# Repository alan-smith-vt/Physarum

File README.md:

# Physarum

Code-first 3D drafting for an ELEGOO Saturn 4 Ultra 16K (resin, 14 × 19 µm pixels).
Designs are Python; output is a printable `.goo`.

## Layout (`slicer_preview/`)

| File | Role |
|---|---|
| `designs/*.py` | One file per design; each defines `PIECES` (and optional `SUPPORTS = True`) |
| `geometry.py` | Primitives: frames, solid columns, base lattice, quad-spiral columns, bridge struts |
| `modifiers.py` | Wrappers that carve existing pieces: chamfer, arches, vaults, grayscale, ID dots |
| `stl_slicer.py` | `stl_piece(path)` — bring in an external mesh |
| `compose.py` | Composites pieces into one volume (shared by preview and export) |
| `supports.py` | TPMS (lidinoid) lattice supports — slow, still experimental |
| `printer.py` | Printer specs + preview downsample factor |

## Workflow

```
cd slicer_preview
cp designs/template.py designs/my_part.py   # edit PIECES
python generate.py my_part                  # preview data (8× downsampled)
python server.py                            # → http://localhost:5555
python to_goo.py my_part                    # full-res → out/my_part.goo
python sdcp.py upload out/my_part.goo       # send to the printer over the network
python sdcp.py print my_part.goo --yes      # start it (ask the user first)
```

**Getting a print to the printer:** always `sdcp.py` (SDCP V3 over the LAN; full command list in its docstring:
status, files, watch, camera, ...). The printer's USB port is dead and we don't use the Elegoo software, so the
network is the only path. Printer last seen at 192.168.0.4; `sdcp.py discover` finds it.
Check the upload printed "Uploaded ..." before `print`: `print` starts whatever file of that name is already on
the printer, so a failed upload silently reprints the old version. Give each revision its own file name (e.g.
`part_v3.goo`), and check `status` shows the expected `TotalLayer`.

Coordinates are mm; X/Z = plate plane, Y = up.

## Notes

- `designs/whiteboard_box.py` printed great (Mar 2026) — good reference for lattice walls.
- `to_goo.py` keeps the template `.goo`'s bottom exposure on purpose. The Julia print's
  custom 30 s base fused it to the plate.
- `archive/`: the failed Julia print (generation takes ~16 h — don't rerun casually),
  decorative geometry (ropes/braids/textured columns), old outputs.

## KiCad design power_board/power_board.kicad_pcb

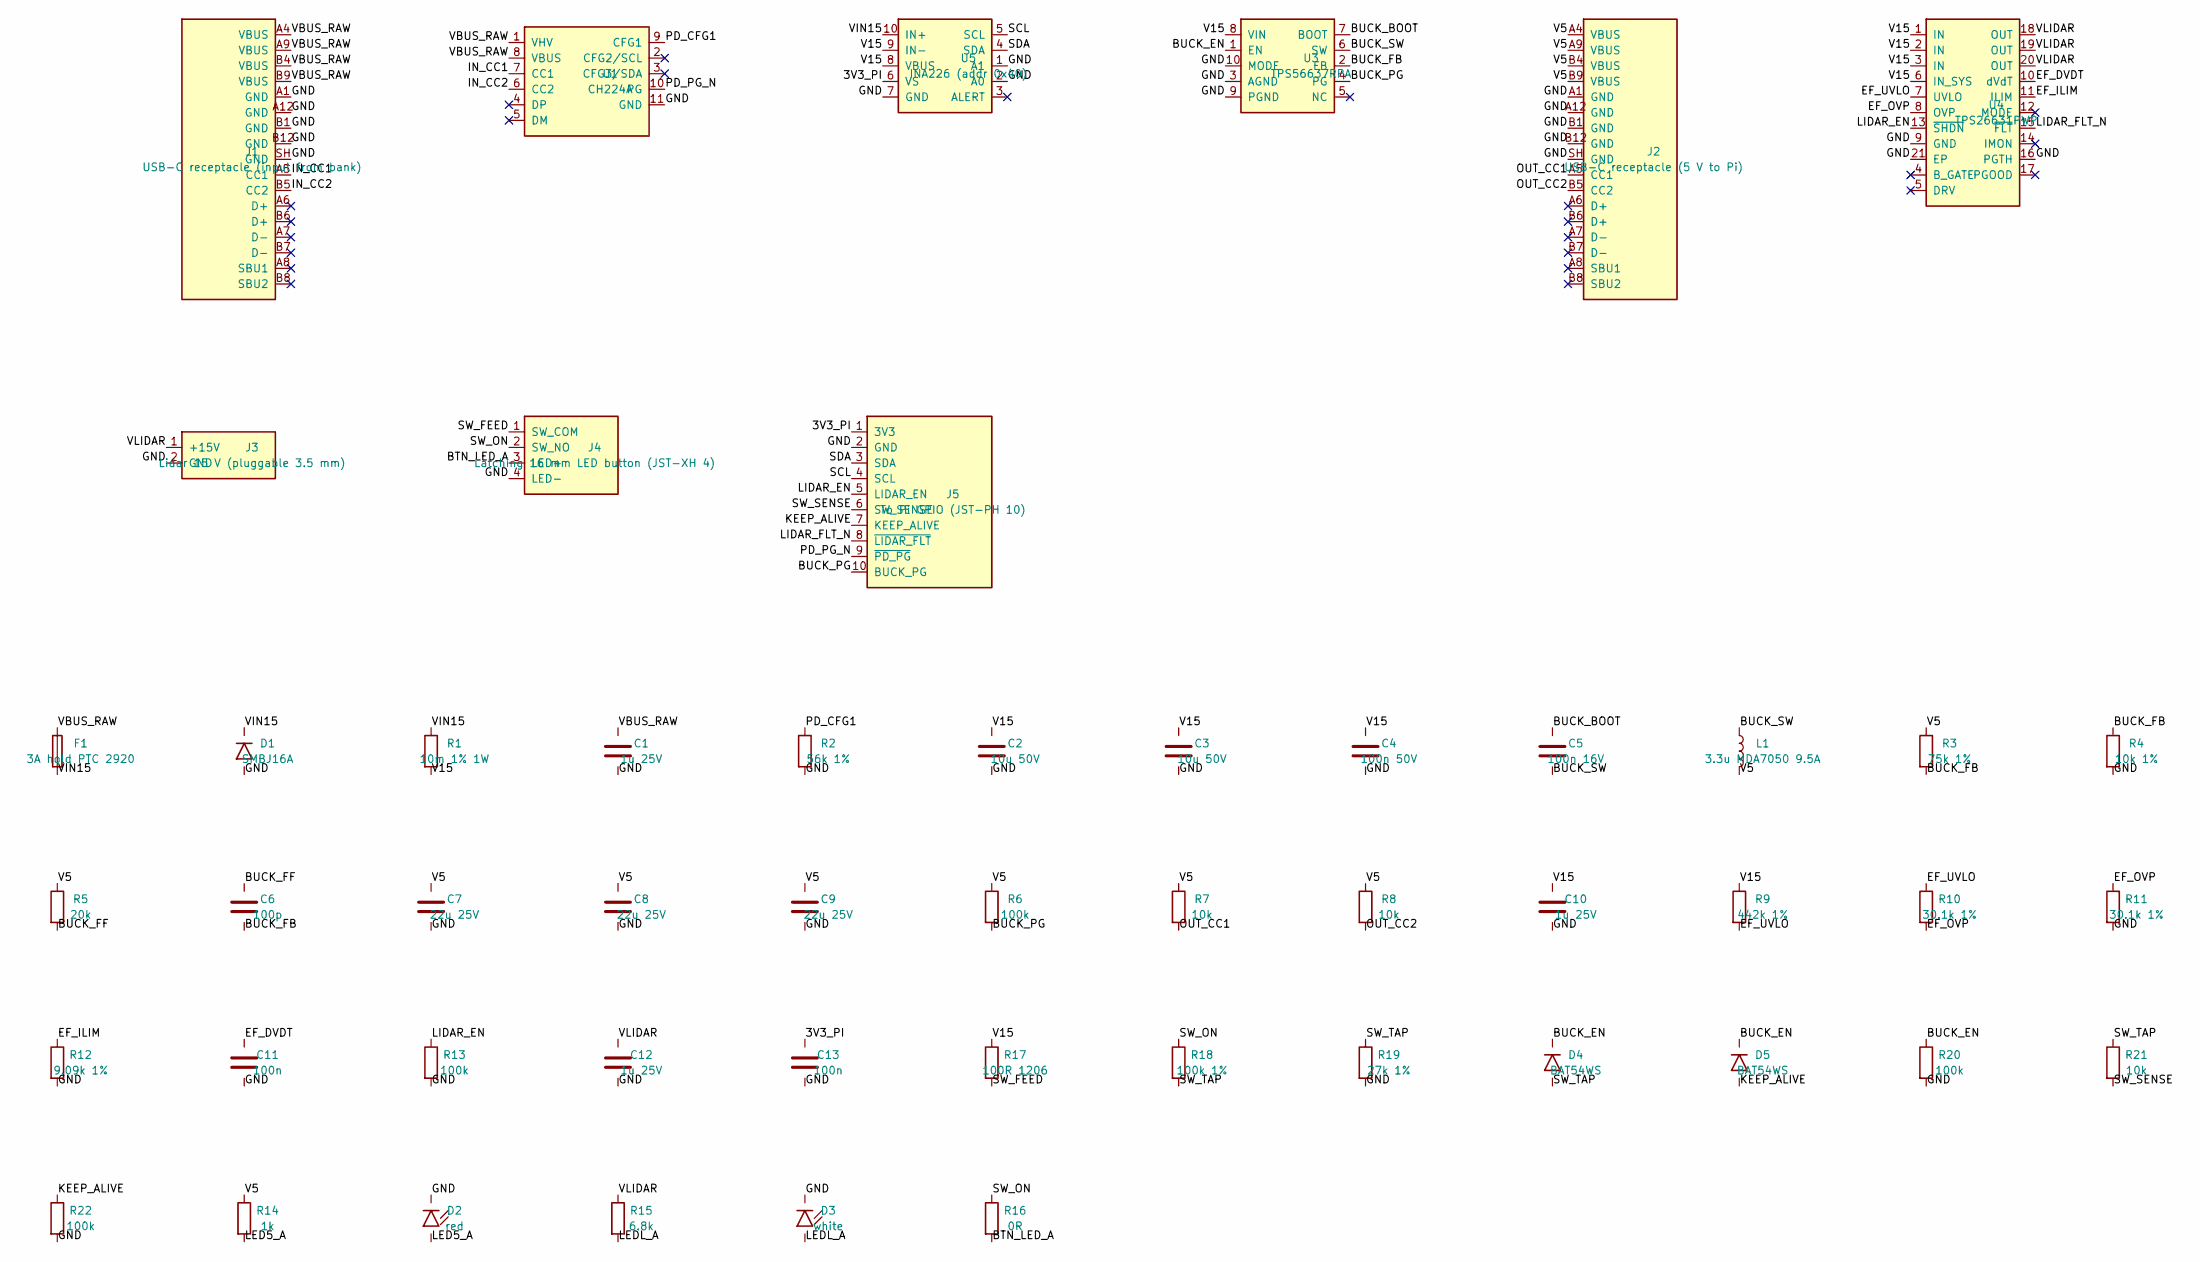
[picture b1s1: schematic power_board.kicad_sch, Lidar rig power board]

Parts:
C1, C10, C12: 1u 25V; C_0805_2012Metric
C2, C3: 10u 50V; C_1210_3225Metric
C4: 100n 50V; C_0603_1608Metric
C5: 100n 16V; C_0603_1608Metric
C6: 100p; C_0603_1608Metric
C7, C8, C9: 22u 25V; C_1210_3225Metric
C11, C13: 100n; C_0603_1608Metric
D1: SMBJ16A; D_SMB
D2: red; LED_0603_1608Metric
D3: white; LED_0603_1608Metric
D4, D5: BAT54WS; D_SOD-323
F1: 3A hold PTC 2920; Fuse_2920_7451Metric
J1: USB-C receptacle (input from bank); USB_C_Receptacle_HRO_TYPE-C-31-M-12
J2: USB-C receptacle (5 V to Pi); USB_C_Receptacle_HRO_TYPE-C-31-M-12
J3: Lidar 15 V (pluggable 3.5 mm); PhoenixContact_MCV_1,5_2-G-3.5_1x02_P3.50mm_Vertical
J4: Latching 16 mm LED button (JST-XH 4); JST_XH_B4B-XH-A_1x04_P2.50mm_Vertical
J5: To Pi GPIO (JST-PH 10); JST_PH_B10B-PH-K_1x10_P2.00mm_Vertical
L1: 3.3u MDA7050 9.5A; L_KOHERelec_MDA7030
R1: 10m 1% 1W; R_2512_6332Metric
R2: 56k 1%; R_0603_1608Metric
R3: 75k 1%; R_0603_1608Metric
R4: 10k 1%; R_0603_1608Metric
R5: 20k; R_0603_1608Metric
R6, R13, R20, R22: 100k; R_0603_1608Metric
R7, R8, R21: 10k; R_0603_1608Metric
R9: 442k 1%; R_0603_1608Metric
R10, R11: 30.1k 1%; R_0603_1608Metric
R12: 9.09k 1%; R_0603_1608Metric
R14: 1k; R_0603_1608Metric
R15: 6.8k; R_0603_1608Metric
R16: 0R; R_0603_1608Metric
R17: 100R 1206; R_1206_3216Metric
R18: 100k 1%; R_0603_1608Metric
R19: 27k 1%; R_0603_1608Metric
U1: CH224A; SSOP-10-1EP_3.9x4.9mm_P1mm_EP2.1x3.3mm
U3: TPS56637RPA; RPA0010A
U4: TPS26631PWP; HTSSOP-20-1EP_4.4x6.5mm_P0.65mm_EP3.4x6.5mm_Mask2.96x2.96mm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
U5: INA226 (addr 0x40); MSOP-10_3x3mm_P0.5mm

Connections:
/3V3_PI: C13.1, J5.1 (3V3), U5.6 (VS)
/BTN_LED_A: J4.3 (LED+), R16.2
/BUCK_BOOT: C5.1, U3.7 (BOOT)
/BUCK_EN: D4.1, D5.1, R20.1, U3.1 (EN)
/BUCK_FB: C6.2, R3.2, R4.1, U3.2 (FB)
/BUCK_FF: C6.1, R5.2
/BUCK_PG: J5.10 (BUCK_PG), R6.2, U3.4 (PG)
/BUCK_SW: C5.2, L1.1, U3.6 (SW)
/EF_DVDT: C11.1, U4.10 (dVdT)
/EF_ILIM: R12.1, U4.11 (ILIM)
/EF_OVP: R10.2, R11.1, U4.8 (OVP)
/EF_UVLO: R9.2, R10.1, U4.7 (UVLO)
/GND: C1.2, C2.2, C3.2, C4.2, C7.2, C8.2, C9.2, C10.2, C11.2, C12.2, C13.2, D1.2, D2.1, D3.1, J1.A1 (GND), J1.A12 (GND), J1.B1 (GND), J1.B12 (GND), J1.SH (GND), J2.A1 (GND), J2.A12 (GND), J2.B1 (GND), J2.B12 (GND), J2.SH (GND), J3.2 (GND), J4.4 (LED-), J5.2 (GND), R2.2, R4.2, R11.2, R12.2, R13.2, R19.2, R20.2, R22.2, U1.11 (GND), U3.3 (AGND), U3.9 (PGND), U3.10 (MODE), U4.9 (GND), U4.16 (PGTH), U4.21 (EP), U5.1 (A1), U5.2 (A0), U5.7 (GND)
/IN_CC1: J1.A5 (CC1), U1.7 (CC1)
/IN_CC2: J1.B5 (CC2), U1.6 (CC2)
/KEEP_ALIVE: D5.2, J5.7 (KEEP_ALIVE), R22.1
/LED5_A: D2.2, R14.2
/LEDL_A: D3.2, R15.2
/LIDAR_EN: J5.5 (LIDAR_EN), R13.1, U4.13 (~SHDN)
/LIDAR_FLT_N: J5.8 (~LIDAR_FLT), U4.15 (~FLT)
/OUT_CC1: J2.A5 (CC1), R7.2
/OUT_CC2: J2.B5 (CC2), R8.2
/PD_CFG1: R2.1, U1.9 (CFG1)
/PD_PG_N: J5.9 (~PD_PG), U1.10 (PG)
/SCL: J5.4 (SCL), U5.5 (SCL)
/SDA: J5.3 (SDA), U5.4 (SDA)
/SW_FEED: J4.1 (SW_COM), R17.2
/SW_ON: J4.2 (SW_NO), R16.1, R18.1
/SW_SENSE: J5.6 (SW_SENSE), R21.2
/SW_TAP: D4.2, R18.2, R19.1, R21.1
/V5: C7.1, C8.1, C9.1, J2.A4 (VBUS), J2.A9 (VBUS), J2.B4 (VBUS), J2.B9 (VBUS), L1.2, R3.1, R5.1, R6.1, R7.1, R8.1, R14.1
/V15: C2.1, C3.1, C4.1, C10.1, R1.2, R9.1, R17.1, U3.8 (VIN), U4.1 (IN), U4.2 (IN), U4.3 (IN), U4.6 (IN_SYS), U5.8 (VBUS), U5.9 (IN-)
/VBUS_RAW: C1.1, F1.1, J1.A4 (VBUS), J1.A9 (VBUS), J1.B4 (VBUS), J1.B9 (VBUS), U1.1 (VHV), U1.8 (VBUS)
/VIN15: D1.1, F1.2, R1.1, U5.10 (IN+)
/VLIDAR: C12.1, J3.1 (+15V), R15.1, U4.18 (OUT), U4.19 (OUT), U4.20 (OUT)

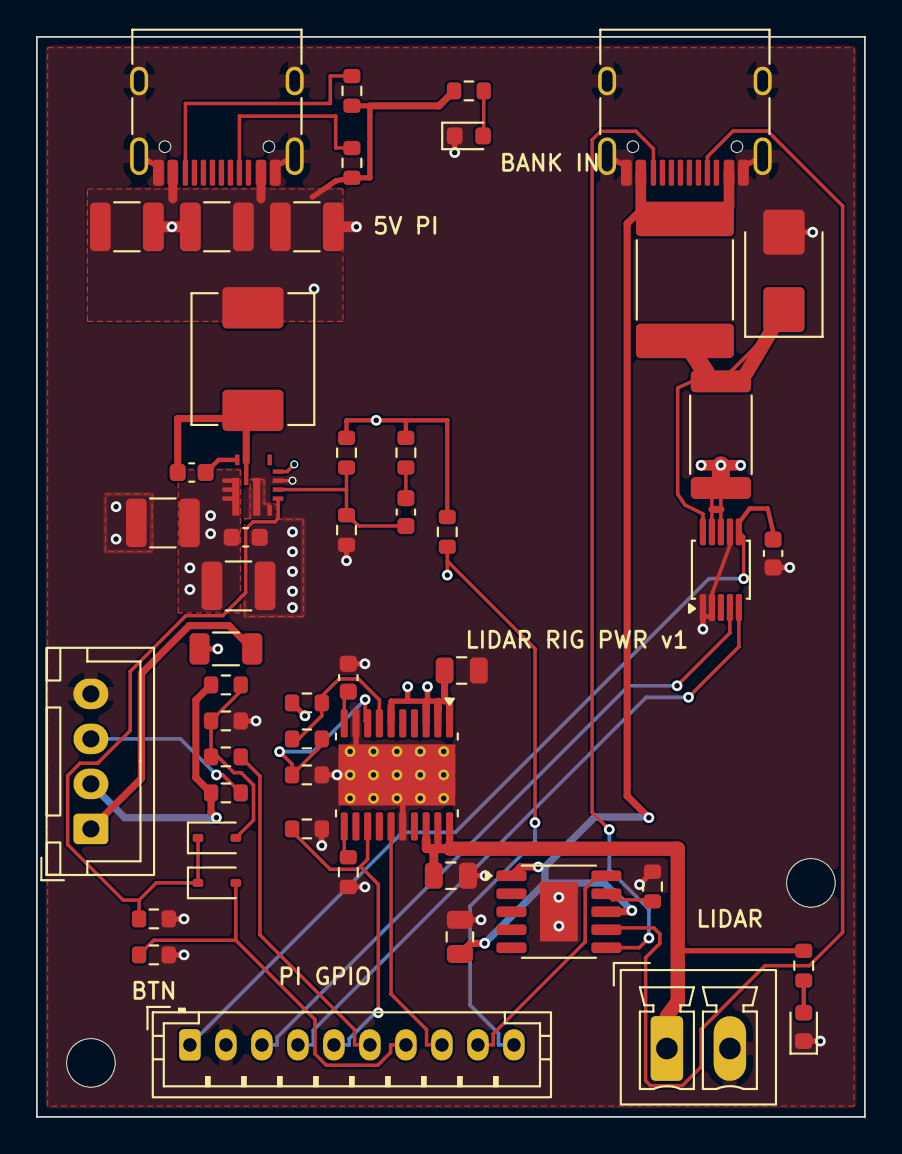
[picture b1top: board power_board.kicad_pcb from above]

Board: 4 copper layers, 46.0 x 60.0 mm, 53 parts (0 on the bottom side), 35 nets.

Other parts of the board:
H1, H2: MountingHole_2.7mm_M2.5

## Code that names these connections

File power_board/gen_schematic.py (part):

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    # INA226
    ("C13", "C", "100n", FP_C, "3V3_PI", "GND", "INA226 VS"),
    # Soft power with the latching switch: buck EN = switch OR Pi keep-alive (diode-OR).
    # Switch on: 15 V -> 100k/27k -> 3.19 V (safe for a Pi GPIO). Switch off: Pi sees SW_SENSE low,
    # shuts down, and drops KEEP_ALIVE at halt (gpio-poweroff), which turns the buck off.
    ("R17", "R", "100R 1206", "Resistor_SMD:R_1206_3216Metric", "V15", "SW_FEED", "limits a short in the switch lead; button LED (~10 mA) drops ~1 V"),
    ("R18", "R", "100k 1%", FP_R, "SW_ON", "SW_TAP", "switch divider top"),
    ("R19", "R", "27k 1%", FP_R, "SW_TAP", "GND", "switch divider bottom: 3.19 V"),
    ("D4", "D", "BAT54WS", "Diode_SMD:D_SOD-323", "BUCK_EN", "SW_TAP", "switch -> EN"),
    ("D5", "D", "BAT54WS", "Diode_SMD:D_SOD-323", "BUCK_EN", "KEEP_ALIVE", "Pi keep-alive -> EN"),
    ("R20", "R", "100k", FP_R, "BUCK_EN", "GND", "EN off when neither drives"),
    ("R21", "R", "10k", FP_R, "SW_TAP", "SW_SENSE", "series into Pi GPIO"),
    ("R22", "R", "100k", FP_R, "KEEP_ALIVE", "GND", "keep-alive low while Pi boots"),
    # Status LEDs
    ("R14", "R", "1k", FP_R, "V5", "LED5_A", ""),
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# side: "L" or "R"
ICS = [
    ("J1", "USB_C_SINK", "USB-C receptacle (input from bank)", "Connector_USB:USB_C_Receptacle_HRO_TYPE-C-31-M-12",
     usb_pins("VBUS_RAW", "IN_CC1", "IN_CC2", None, None, "R")),
    # CH224A: same function as the CH224Q in ESSOP-10 (hand-reworkable). CFG2/CFG3 have internal
    # 10k pull-ups to the chip's own rail, so they stay floating: tying them to the Pi's I2C would
    # back-power the Pi's 3V3 while the Pi is off. The INA226 reads the bus voltage instead.
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        ("4", "PG", "BUCK_PG", "R"), ("5", "NC", None, "R"),
    ]),
    ("J2", "USB_C_SOURCE", "USB-C receptacle (5 V to Pi)", "Connector_USB:USB_C_Receptacle_HRO_TYPE-C-31-M-12",
     usb_pins("V5", "OUT_CC1", "OUT_CC2", None, None, "L")),
    ("U4", "TPS26631", "TPS26631PWP", "Package_SO:HTSSOP-20-1EP_4.4x6.5mm_P0.65mm_EP3.4x6.5mm_Mask2.96x2.96mm_ThermalVias", [
        ("1", "IN", "V15", "L"), ("2", "IN", "V15", "L"), ("3", "IN", "V15", "L"),
        ("6", "IN_SYS", "V15", "L"), ("7", "UVLO", "EF_UVLO", "L"), ("8", "OVP", "EF_OVP", "L"),
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
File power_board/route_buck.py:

"""Route the TPS56637 buck on power_board.kicad_pcb (run after gen_board.py, with KiCad's Python).

Follows the datasheet layout guide (SLVSEG1A 10.1):
  - VIN loop: F.Cu V15 pour joining C3/C2/C4 to the pin-8 bar and fingers; C2 and C4 span VIN-PGND
    directly under the chip, their GND side in an F.Cu GND pour with stitching vias to In1/B.Cu.
  - SW: short 0.4 mm stub from pin 6 into L1, boot cap C5 beside pin 7.
  - VOUT: F.Cu V5 pour from L1 across the output caps to J2's VBUS pins.
  - FB: pin 2 straight to the R3/R4 column on the quiet side; separate V5 sense from the output pour
    to the top of R3/R5 on In2; AGND (pin 3) gets its own via to the ground planes.
  - EN and PG escape to In2 vias for routing later with the rest of the board.
Coordinates are board mm (origin top-left), matching gen_board.PLACE.
"""
from pathlib import Path

import pcbnew

PCB = Path(__file__).with_name("power_board.kicad_pcb")
board = pcbnew.LoadBoard(str(PCB))
GROUP = "buck-route"


def mm(v):
    return pcbnew.FromMM(v)


def net(name):
    n = board.FindNet(f"/{name}")
    if n is None:
        raise SystemExit(f"no net {name}")
    return n


# start clean: drop anything this script made before
for item in list(board.Tracks()) + list(board.Zones()):
    if item.GetParentGroup() and item.GetParentGroup().GetName() == GROUP:
        board.Remove(item)
for g in list(board.Groups()):
    if g.GetName() == GROUP:
        board.Remove(g)
group = pcbnew.PCB_GROUP(board)
group.SetName(GROUP)
board.Add(group)


def track(netname, pts, width, layer=pcbnew.F_Cu):
    for (x1, y1), (x2, y2) in zip(pts, pts[1:]):
        t = pcbnew.PCB_TRACK(board)
        t.SetStart(pcbnew.VECTOR2I(mm(x1), mm(y1)))
        t.SetEnd(pcbnew.VECTOR2I(mm(x2), mm(y2)))
        t.SetWidth(mm(width))
        t.SetLayer(layer)
        t.SetNet(net(netname))
        t.SetLocked(True)
        board.Add(t)
        group.AddItem(t)


def via(netname, x, y, d=0.6, drill=0.3):
    v = pcbnew.PCB_VIA(board)
    v.SetPosition(pcbnew.VECTOR2I(mm(x), mm(y)))
    v.SetWidth(mm(d))
    v.SetDrill(mm(drill))
    v.SetNet(net(netname))
    v.SetLocked(True)
    board.Add(v)
    group.AddItem(v)


def pour(netname, pts, layer=pcbnew.F_Cu, clearance=0.2, priority=10):
    z = pcbnew.ZONE(board)
    z.SetLayer(layer)
    z.SetNet(net(netname))
    ol = z.Outline()
    ol.NewOutline()
    for x, y in pts:
        ol.Append(mm(x), mm(y))
    z.SetLocalClearance(mm(clearance))
    z.SetMinThickness(mm(0.2))
    z.SetPadConnection(pcbnew.ZONE_CONNECTION_FULL)
    z.SetAssignedPriority(priority)
    board.Add(z)
    group.AddItem(z)


# ── VIN (V15) loop ──
pour("V15", [(7.85, 24.05), (11.3, 24.05), (11.3, 32.0), (7.85, 32.0)])
for x, y in [(9.65, 26.6), (9.65, 27.6), (8.5, 29.5), (8.5, 30.7)]:   # VIN pour down to the In2 V15 plane
    via("V15", x, y)
pour("GND", [(11.85, 24.6), (12.62, 24.6), (12.62, 25.95), (13.3, 25.95), (13.3, 26.8), (14.8, 26.8),
             (14.8, 32.2), (11.55, 32.2), (11.55, 26.75), (11.85, 26.75)], clearance=0.15)
for y in (27.5, 28.6, 29.7, 30.8, 31.7):
    via("GND", 14.2, y)
# bulk cap C3's GND side
pour("GND", [(3.8, 25.4), (6.4, 25.4), (6.4, 28.6), (3.8, 28.6)])
via("GND", 4.4, 26.1)
via("GND", 4.4, 27.9)

# ── SW node and boot cap (C5 between L1 and the chip: pad 2 = SW on the left, pad 1 = BOOT on the right) ──
track("BUCK_SW", [(11.63, 23.6), (11.63, 21.5)], 0.4)          # pin 6 up into L1 pad 1
track("BUCK_SW", [(7.82, 24.2), (7.82, 21.2), (10.8, 21.2)], 0.4)   # C5 SW side up into L1 pad 1
track("BUCK_BOOT", [(9.38, 24.2), (10.1, 23.5), (11.13, 23.5)], 0.25)  # C5 boot side to pin 7

# ── VOUT (V5) ──
pour("V5", [(2.8, 8.45), (17.0, 8.45), (17.0, 15.8), (2.8, 15.8)])
track("V5", [(12.45, 7.54), (12.45, 9.0)], 0.5)                  # J2 A4/B9
track("V5", [(7.55, 7.54), (7.55, 9.0)], 0.5)                    # J2 A9/B4
track("GND", [(6.47, 10.55), (8.53, 10.55)], 0.6)              # C7 + C8 GND pads
via("GND", 7.5, 10.55)
track("GND", [(16.48, 10.55), (17.75, 10.55)], 0.6)            # C9 GND
via("GND", 17.75, 10.55)

# ── feedback ──
track("BUCK_FB", [(13.4, 25.15), (17.2, 25.15)], 0.2)          # pin 2 to the divider column
track("BUCK_FB", [(17.2, 23.93), (17.2, 26.57)], 0.2)          # R3 bottom - R4 top
track("BUCK_FB", [(17.2, 26.57), (17.9, 27.17), (20.5, 27.17)], 0.2)   # R4 top to C6 bottom (feed-forward)
track("BUCK_FF", [(20.5, 23.93), (20.5, 25.63)], 0.2)          # R5 bottom to C6 top
track("GND", [(17.2, 28.23), (17.2, 29.1)], 0.3)               # R4 bottom
via("GND", 17.2, 29.1)
track("GND", [(13.4, 24.65), (14.2, 24.65)], 0.2)              # AGND (pin 3) to its own via
via("GND", 14.2, 24.65, d=0.45, drill=0.3)
# V5 sense: from the output pour on In2 to the top of R3 and R5
via("V5", 15.4, 14.0)
track("V5", [(15.4, 14.0), (18.85, 14.0), (18.85, 21.3)], 0.25, pcbnew.In2_Cu)
via("V5", 18.85, 21.3)
track("V5", [(17.2, 22.27), (17.2, 21.3), (20.5, 21.3), (20.5, 22.27)], 0.25)

# ── J2 (5 V to the Pi): GND pins to the shell, CC pull-ups (R7 = CC1 lower, R8 = CC2 upper) ──
track("GND", [(13.25, 7.2), (14.32, 6.63)], 0.3)
track("GND", [(6.75, 7.2), (5.68, 6.63)], 0.3)
track("OUT_CC1", [(11.25, 7.54), (11.25, 4.4), (16.6, 4.4), (16.6, 6.17), (17.5, 6.17)], 0.2)   # between the shell pads
track("OUT_CC2", [(8.25, 7.54), (8.25, 3.7), (16.3, 3.7), (16.3, 2.17), (17.5, 2.17)], 0.2)
track("V5", [(17.5, 3.83), (18.5, 3.83), (18.5, 7.83), (17.5, 7.83)], 0.3)   # Rp tops together
track("V5", [(17.5, 7.83), (16.6, 8.0), (15.3, 8.9)], 0.3)                    # into the V5 pour

# ── PG pull-up R6 (V5 top, PG bottom) ──
track("V5", [(20.5, 21.3), (22.8, 21.3), (22.8, 26.67)], 0.25)

# ── EN / PG escapes (EN and PG to J5 are finished with the rest of the board) ──
track("BUCK_PG", [(13.4, 24.15), (13.9, 24.15), (14.3, 23.75)], 0.2)
via("BUCK_PG", 14.3, 23.75, d=0.45, drill=0.3)
track("BUCK_PG", [(14.3, 23.75), (14.9, 23.75), (14.9, 29.9), (22.8, 29.9)], 0.2, pcbnew.In2_Cu)
via("BUCK_PG", 22.8, 29.9)
track("BUCK_PG", [(22.8, 29.9), (22.8, 28.33)], 0.2)

board.Save(str(PCB))
print("buck routed:", sum(1 for i in group.GetItems()), "items")

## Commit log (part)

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2026-03-22 Added files
2026-03-22 Validated thickening logic
2026-03-22 Added thickness calculation and polling updates
2026-03-23 Stable with concurrent multi filament
2026-03-26 Moved to lattice structures
2026-03-29 New stuff
2026-03-29 Who knows
2026-04-01 Extra arches
2026-04-01 Please
2026-04-01 Thicker columns at base
2026-04-01 box_v2!
2026-04-02 Add tree support structure generator for 3D printing
    Cura-inspired tree support algorithm that detects overhangs, builds
    branching supports with attraction/merge, tip taper, and base flare.
    Usable standalone (re-encodes _slices.bin) or as importable module.
    https://claude.ai/code/session_01TD2Uy1zgb4m2ZhwZMC6uyE
2026-04-02 Add GENERATE_SUPPORTS flag to generate.py
    When set to True, tree supports are generated and included in the
    output automatically — no need to run a separate script.
    https://claude.ai/code/session_01TD2Uy1zgb4m2ZhwZMC6uyE
2026-04-02 Add GENERATE_SUPPORTS flag and make_global_slice to generate_julia.py
    Same support integration as generate.py — set GENERATE_SUPPORTS = True
    to include tree supports in the Julia set output.
    https://claude.ai/code/session_01TD2Uy1zgb4m2ZhwZMC6uyE
2026-04-02 Rewrite supports: two-pass centerline/radius, distinct grayscale
    Pass 1 builds centerlines tracking only positions and merge weight
    (number of original tips absorbed). Pass 2 walks the skeleton and
    assigns radii from topology: weight → area-preserving sqrt scaling,
    tip taper near contact, base flare near build plate.
    - Supports render at gray 128 (model uses 255) so they're visually
    distinct in the viewer
2026-04-02 Fix floating supports: angle-limited attraction, tiny merge distance
    The root cause was that branches were "teleporting" on merge — two
    columns 5mm apart would snap to an averaged position, leaving the
    upper one floating. Now branches physically curve toward each other:
    - Lateral movement capped by MAX_BRANCH_ANGLE_DEG (40°) so each
    layer step is at most tan(40°)*LY_MM ≈ 0.067mm
    - MERGE_DISTANCE_MM reduced from 5.0 to 0.3mm — branches only merge
2026-04-02 Collision-check branches against model during descent
    Branches that drift laterally into solid model geometry are now
    killed at that layer. Previously only the original overhang pixel's
    floor was checked, so branches that curved via attraction could
    penetrate the part below.
    Each layer of the descent does a pixel lookup of each branch's
    current position against make_global_slice — if the model is solid
2026-04-02 Blue island overlay, teal supports, remove base jet colormap
    - Detect ALL overhang pixels (not just subsampled) and overlay them
    on the model with value 5 (viewer maps values 1-10 to bright blue)
    - Viewer: value 128 now renders teal instead of warm amber (was
    showing brown because 128/255 went through the amber tint path)
    - Viewer: removed the 2mm jet colormap at the base, replaced with
    explicit value-based coloring: 1-10=blue islands, 128=teal supports,
2026-04-03 Rewrite supports: lattice-fill-then-subtract approach
    Replace tree support algorithm with lattice-based approach:
    1. Fill model bounding box with a grid lattice (vertical columns +
    horizontal ties + diagonal zigzag bracing)
    2. Subtract a dilated clearance shell around the model (2 layers
    vertical, 0.5mm lateral)
    3. Output remaining lattice as support piece at gray 128 (teal)
2026-04-03 Fix Julia set clipping and missing build plate/axes
    - Expand Julia quaternion space from [-1,1]³ to [-1.6,1.6]³ via QSPACE
    parameter. The filled Julia set for c=[-0.2,0.8,0,0] extends to
    |q|≈1.54, so [-1,1] was clipping features at the edges and top.
    - Add plate_w_mm and plate_h_mm to generate_julia.py meta output.
    These were missing, causing the viewer's build plate, grid, and axis
    indicators to get NaN coordinates and disappear.
2026-04-03 Lower Julia set by 4mm to sit on build plate
    https://claude.ai/code/session_01TD2Uy1zgb4m2ZhwZMC6uyE
2026-04-03 Speed up lattice supports: pre-cache model, height-map culling
    - Pass 1: scan all model slices once, cache in memory, build height
    map (max solid layer per pixel)
    - Pass 2: generate lattice only below model surface per pixel
    (height-map cull), subtract clearance from cached slices
    - Reduced clearance: 1 layer vertical (was 2), 0.2mm XZ (was 0.5mm)
    - Precompute lattice masks once instead of per-layer
2026-04-03 Disable height-map cull to isolate floating support issue
    https://claude.ai/code/session_01TD2Uy1zgb4m2ZhwZMC6uyE
2026-04-03 Re-enable height map, add floater detection pass (blue)
    Pass 3 does a bottom-up flood fill to find disconnected support:
    - Layer 0: all support pixels are "grounded" (connected to plate)
    - Each subsequent layer: seed from pixels connected below, then
    iteratively dilate within the layer through support pixels until
    stable (propagates through horizontal ties between columns)
    - Any support pixel not reached = floater, colored FLOATER_GRAY (5)
2026-04-03 Classify floaters: model-grounded (yellow) vs disconnected (blue)
    Pass 3 now does two flood fills:
    A) Bottom-up from build plate — finds plate-grounded support (teal)
    B) Bottom-up from model surfaces — support pixels sitting on model
    (model solid at layer-1) seed a second flood fill upward
    Three support colors in viewer:
    - Teal (128): connected to build plate
2026-04-03 Cell-aware height culling: treat grid cells as composite units
    Instead of per-pixel height culling (which slices through ties and
    diagonals mid-span), compute a coarse height map per grid cell, then
    dilate by 1 cell in all directions (3x3 max). A column keeps all its
    connected ties as long as any neighboring cell has model above.
    Expand the dilated cell heights back to a per-pixel effective height
    map used for the cull. This prevents partial removal of horizontal
2026-04-03 Replace grid lattice with lidinoid TPMS
    Swap the grid+tie+diagonal lattice for a lidinoid triply periodic
    minimal surface. The implicit function:
    sin(2x)cos(y)sin(z) + sin(2y)cos(z)sin(x) + sin(2z)cos(x)sin(y)
    is evaluated per-layer with |f| < threshold giving solid voxels.
    Period = LATTICE_SPACING_MM, wall thickness controlled by
    TPMS_THRESHOLD (0.3 default).
2026-04-03 Remove cell-aware height culling, use simple per-pixel height map
    TPMS is continuous so partial culling at boundaries doesn't create
    disconnected fragments like the grid lattice did. Simple per-pixel
    height_map cull is sufficient and faster.
    https://claude.ai/code/session_01TD2Uy1zgb4m2ZhwZMC6uyE
2026-04-03 Delete floaters, volume-filter model-grounded islands
    - Blue floaters (disconnected): deleted immediately, no longer rendered
    - Model-grounded floaters: connected component analysis via union-find
    tracks volume in mm³ per component. Components below
    MIN_MODEL_GROUNDED_VOL_MM3 (0.5mm³) are deleted. Threshold is
    resolution-agnostic (converted to voxel count from PX*PZ*LY).
    - Surviving model-grounded components stay yellow (200)
2026-04-03 Cache Julia slices — eliminates duplicate computation
    Each make_slice call does 16 iterations of quaternion math on the
    full image. Slices were being computed twice: once in support pass 1
    and again in encode_all. Adding a per-layer cache dict inside the
    piece closure should roughly halve total runtime.
    https://claude.ai/code/session_01TD2Uy1zgb4m2ZhwZMC6uyE
2026-04-03 Speed up Julia + supports: 3 optimizations
    Julia make_slice:
    - Early layer termination: skip entire layers where |qy| > bail_r
    (theoretical Julia set bound). Empty top/bottom layers return
    instantly without allocating arrays.
    - Per-pixel bail-out: pixels where |q|² > bail_r² are pre-marked as
    escaped before iteration, skipping obviously-outside regions.
2026-04-03 Fix NameError: model_slices → N_SLICES bounds check
    https://claude.ai/code/session_01TD2Uy1zgb4m2ZhwZMC6uyE
2026-04-03 Bump TPMS period from 3mm to 5mm
    Less dense lattice — fewer voxels, easier removal, less resin.
    Tune at supports.py line 33: LATTICE_SPACING_MM
    https://claude.ai/code/session_01TD2Uy1zgb4m2ZhwZMC6uyE
2026-04-03 Multiprocess + reduced-res scan for full-resolution support
    supports.py:
    - Pass 1 scans model at SCAN_SCALE=4× spatial downsample + every 4th
    layer. Height map built at scan res, upsampled to full res. Model
    clearance cached at scan res, upsampled + fine-dilated for pass 2.
    At 1x resolution this scans 1/64th the voxels.
    - Pass 2 parallelised across N_WORKERS=8 cores. Each worker generates
2026-04-03 Native low-res scan piece for fast pass 1, revert to 3mm TPMS
    The bottleneck was that pass 1 called make_slice at full resolution
    (4286×3158) then downsampled — the expensive Julia computation still
    ran at full res.
    Now generate_julia.py builds a second Julia piece at SCAN_SCALE×
    coarser resolution (temporarily patching printer constants). This
    scan piece is passed to generate_supports via make_scan_slice, so
2026-04-03 Set PREVIEW_SCALE=1 (full res), disable supports for Julia test
    https://claude.ai/code/session_01TD2Uy1zgb4m2ZhwZMC6uyE
2026-04-03 Parallel encoding with ThreadPoolExecutor (8 threads)
    Replaces serial encode_all with a threaded sliding-window approach:
    - ThreadPoolExecutor (not multiprocessing) so closures work on Windows
    - NumPy releases the GIL during math, so threads get true parallelism
    for the quaternion iteration
    - Sliding window of ENCODE_WINDOW=32 slices bounds memory (~430MB at 1x)
    - Surface extraction stays serial (needs consecutive layers)
2026-04-03 Fix scan piece: pass pixel sizes as params, not monkey-patch
    The low-res scan piece was running at full resolution because
    quaternion_julia_piece() reads PX_MM/PZ_MM/LY_MM from its import
    binding, not from the printer module object. Patching printer.PX_MM
    doesn't affect the already-imported name.
    Fix: add px_mm/pz_mm/ly_mm optional parameters to
    quaternion_julia_piece(). The scan piece is now built with:
2026-04-03 Revert to PREVIEW_SCALE=8 — viewer doesn't need 1x
    to_goo.py re-renders at full resolution independently.
    The viewer encoding at 1x would take hours for no benefit.
    https://claude.ai/code/session_01TD2Uy1zgb4m2ZhwZMC6uyE
2026-04-03 Fix STL spam: inline goo_encode_placed, remove to_goo import
    Importing from to_goo.py triggered its module-level
    'from generate import ...' which loads the STL and builds all box
    frame pieces. On Windows each of 8 workers re-imported everything,
    printing the STL message 8 times and wasting work.
    Fix: copy goo_encode_placed directly into to_goo_julia.py so there's
    no dependency on to_goo.py at all.
2026-04-03 Add progress reporting to all pass 3 sub-passes
    Pass 3A (plate flood fill), 3B (model-grounded flood fill), and
    3C (volume filtering) now print progress every 200 layers with
    elapsed time.
    https://claude.ai/code/session_01TD2Uy1zgb4m2ZhwZMC6uyE
2026-04-03 Fix Windows pickle crash: memmap supports + checkpointing
    Two fixes for the encoding stage:
    1. Support slices written to a memory-mapped file (_support_cache.dat)
    instead of passed through Pool initializer. Workers np.memmap the
    file independently — no pickle serialization, no size limit.
    2. Checkpoint file (_julia_checkpoint.pkl) saves completed layer RLEs
    every 50 layers. On crash, re-run picks up where it left off.
2026-04-03 Skip sub-plate layers in .goo output
    With OFFSET_Y_MM=-8.0 the first ~160 layers at 50µm are below the
    build plate (empty). Now computes plate_layer and only encodes/writes
    layers from there up. Layer heights in the .goo start at 0 from the
    first real layer. Saves ~160 blank exposures on the printer.
    https://claude.ai/code/session_01TD2Uy1zgb4m2ZhwZMC6uyE
